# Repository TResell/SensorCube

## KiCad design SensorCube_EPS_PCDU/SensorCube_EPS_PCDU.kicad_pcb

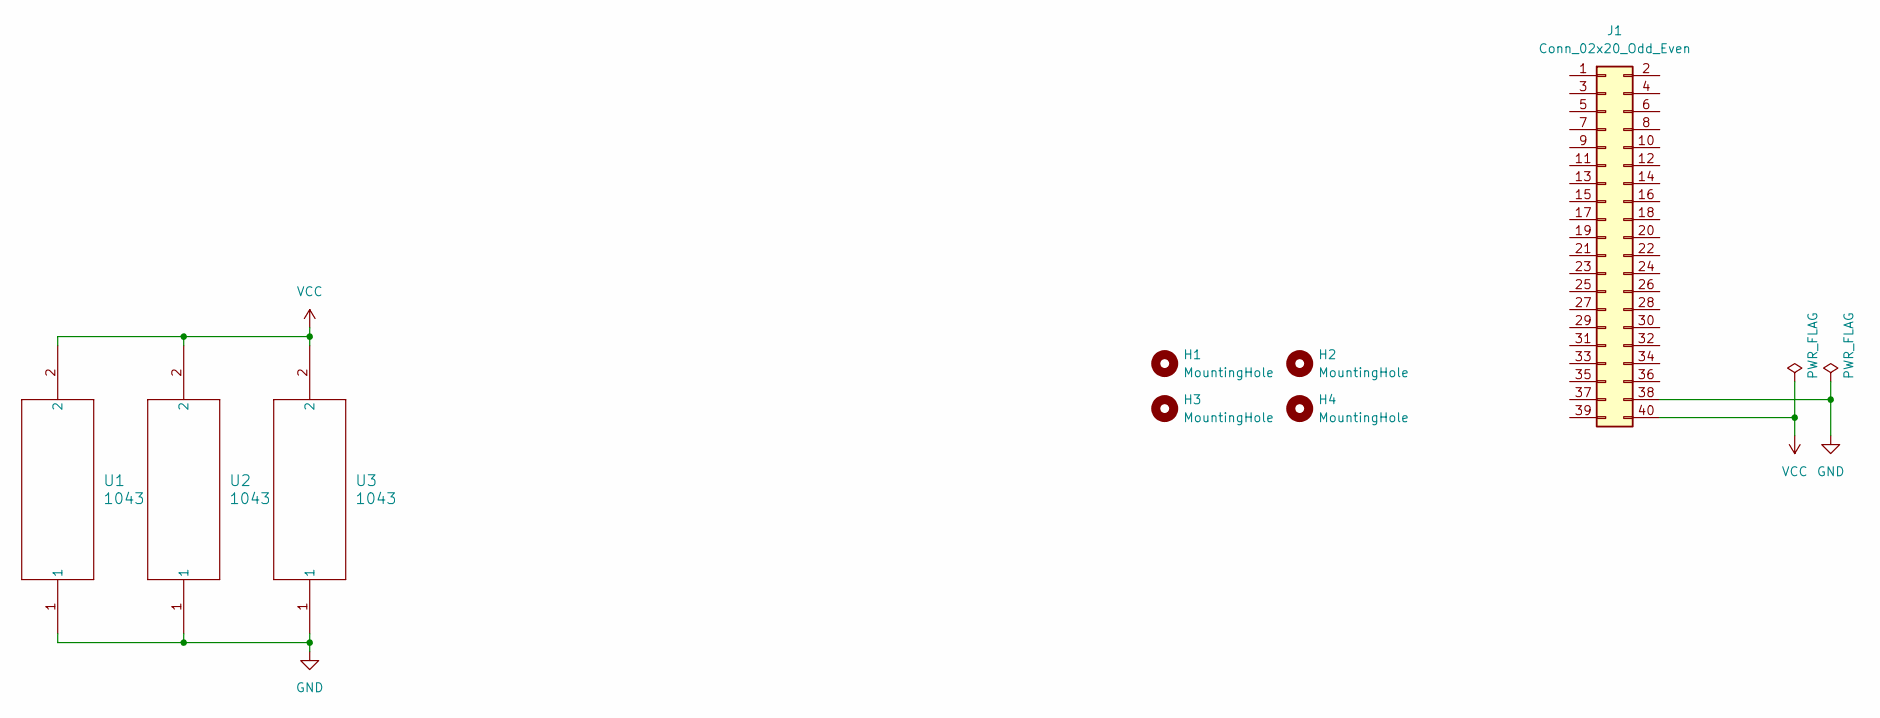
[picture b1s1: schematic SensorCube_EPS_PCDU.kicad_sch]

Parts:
H1, H2, H3, H4: MountingHole; MountingHole_3.2mm_M3_modified
J1: Conn_02x20_Odd_Even; PinHeader_2x20_P2.54mm_Vertical
U1, U2, U3: 1043; 1043_KEY_Modified

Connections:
GND: J1.38, U1.1, U2.1, U3.1
VCC: J1.40, U1.2, U2.2, U3.2

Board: 4 copper layers, 8 parts (3 on the bottom side), 2 nets, no tracks yet.

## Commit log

2024-07-16 Added gitignore file
2024-07-16 Added git-branch image file
2025-04-14 Added various images
2025-04-14 Start of EPS module
2025-04-14 Added template schematic
